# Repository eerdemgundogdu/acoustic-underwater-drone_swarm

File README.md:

# Akustik Suru Dugumu (acoustic-underwater-drone_swarm)

Deniz tabanina birakilan, aylarca pille bekleyen pasif akustik dinleme dugumu: gemi/arac gurultusuyle uyanir, pervane imzasini LOFAR ve DEMON ile cikarir, sonucu 24/28 kHz BFSK akustik modemle komsu dugumlere cok atlamali (multi-hop) olarak yayar. Uyku akimini piezo dalga/akinti hasadi destekler.

Sistem uc katmandan olusur:

- Donanim (`hardware/`): Teensy 4.1 tasiyici + hidrofon AFE + uyanma devresi + piezo hasadi + modem H-koprusu (2 katman, 120x95 mm, KiCad 9).
- Firmware (`firmware/`): 192 kHz cift ADC DMA ornekleme, akisli LOFAR/DEMON islemcileri, Goertzel tabanli BFSK alici, SipHash etiketli mesh protokolu ve guc durum makinesi.
- Model (`dsp/`): Bilesen degerlerinden AFE yaniti, uyku akim butcesi ve akustik baglanti butcesi; sematik ile firmware sabitlerinin tutarliligini test eder.

> **Durum:** Kart Rev A tasarim asamasindadir; uretilmedi ve donanimda test edilmedi. DSP ve modem zinciri sentetik sinyallerle (192 kHz) host testlerinde dogrulandi; firmware Teensy 4.1 icin derlenir. IFF kural seti bir demodur, saha imza kutuphanesi degildir.

## Calisma Dongusu

1. Uykuda yalnizca hep acik alan (~7 uA) calisir: `MCP6042` iki kademe ~60 dB (5..450 Hz) + tepe dedektoru + `TLV7031` karsilastirici.
2. Esik asilinca karsilastirici `LMR16006X` buck'i acar; RC mandal Teensy acilisina (~0.4 s) kadar gucu tutar, Teensy `PWR_HOLD` (pin 23) ile devralir.
3. Teensy, AFE'nin 20 dB ve 40 dB cikislarini ADC0/ADC1'de ayni anda 192 kHz'te DMA ile ornekler; `DualGainSelector` kirpilmayan kanali secer.
4. LOFAR (~2 s) ve DEMON (~2.7 s) sonucu `classify_signature` ile siniflandirilir. Hedef bulunursa dugum kendi TDMA yuvasinda alarm yayinlar.
5. Komsu dugumlerden gelen cerceveler dogrulanir (CRC-16 + SipHash-2-4), TTL > 0 ise tekrar yayinlanir.
6. Son aktiviteden 30 s sonra `PWR_HOLD` birakilir; buck kapanir, kart uykuya doner.

## Firmware (`firmware/`)

- `acoustic_dsp.cpp`: Radix-2 FFT, Hanning, Two-Pass Split-Window CFAR beyazlatma.
  - `LofarProcessor`: 192 kHz -> (4. derece Butterworth, /16) -> (/6) 2 kHz, 1024 noktalik FFT, 4 spektrum ortalamasi, 20..700 Hz tepe arama.
  - `DemonProcessor`: 4..30 kHz bant geciren -> kare-yasasi zarf -> /64 ortalama -> (LP 150 Hz, /8) 375 Hz -> 1024 noktalik FFT. Saft (2.5..11.5 Hz) ve N = 3..7 kanat harmonigi; yanlis alarm olasiligi ~7e-4 olacak sekilde 10 dB esik.
  - `DualGainSelector`: 20/40 dB AFE kanal secimi, kirpilma sonrasi 256 ornek histerezis.
- `dsp_filter.cpp`: RBJ biquad, 4. derece Butterworth, desimatorler.
- `bfsk_modem.cpp`: Verici bit plani (16 bit preamble + cerceve). Alicida 192 noktalik Goertzel (24/28 kHz tonlar + 20/32 kHz bant disi gurultu referansi), ceyrek sembol adimli 4 zamanlama seridi, `0xA55A` senkron kelimesi, verici sirasinda alici susturma.
- `swarm_mesh.cpp`: 20 baytlik cerceve, SipHash-2-4 (128 bit anahtar, 32 bit etiket) + CRC-16-CCITT, (kaynak, sira) halka tamponuyla tekrar eleme, TTL ile cok atlamali aktarim, dugum kimligine gore 250 ms TDMA yuvasi.
- `power_manager.cpp`: `BOOT / LISTEN / SHUTDOWN / FAULT_LEAK / LOW_BATT` durum makinesi; dinleme penceresi, alarm hiz siniri, sizintida periyodik alarm, dusuk pilde kapanma.
- `teensy_node/main.cpp`: Teensy entegrasyonu (`ADC` + `AnalogBufferDMA`, `IntervalTimer` ile sembol sembol BFSK yayini).

## Donanim (`hardware/`)

- 4S Li-ion girisi: 2 A sigorta, seri NC reed kurma anahtari, SS26 ters kutup, SMBJ20CA TVS.
- Hep acik alan: `HT7533-1` (30 V giris, 2.5 uA) ve piezo hasadi (BAT54S kopru + 22 uF + 18 V kiskac + ikinci `HT7533-1`), `BAT54C` diyot-VEYA.
- Uyanma mandali: `WAKE_CMP` VEYA `PWR_HOLD` -> 1 s RC -> `LMR16006X` `EN`.
- Hidrofon AFE: `MCP6022` x2, 20 dB + Sallen-Key 39.7 kHz (Q 0.74) + 20 dB, 100 ohm / 2.2 nF ADC surme ve BAT54S kiskaclari; `LP5907` dusuk gurultulu analog besleme.
- Modem vericisi: `DRV8871`, FlexPWM 24/28 kHz, 62k ILIM (~1 A), DC blok kondansatoru; eslesme trafosu ve projektor kart disi.
- Uykuda sifir akimli pil olcumu (`AO3401A` + `2N7002` yuksek taraf anahtari).

Tasarim hesaplari `hardware/DESIGN.md`, konnektor tablolari `hardware/WIRING.md`, uretim dosyalari (Gerber, BOM, CPL, sematik PDF, DRC raporu) `hardware/output/` altindadir.

## Derleme ve Testler

Donanim olmadan calisan C++ ve Python testleri:

```bash
cmake -S firmware/test -B build/test && cmake --build build/test && ctest --test-dir build/test --output-on-failure

python3 dsp/test_node_model.py
python3 dsp/node_model.py          # AFE yaniti, akim butcesi, baglanti butcesi ozeti
```

Teensy 4.1 derlemesi:

```bash
cd firmware
pio run -e node      # Rev A kart: uyanma/uyku dongusu
pio run -e bench     # Tezgah: USB beslemede surekli uyanik
```

Saha icin suru anahtari uretme:

```bash
python3 scripts/gen_swarm_key.py      # build_flags satirini yazar
```

Tezgah testi adimlari: `docs/tezgah_testi.md`.

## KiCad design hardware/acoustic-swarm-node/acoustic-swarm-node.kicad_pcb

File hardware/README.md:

# Akustik Suru Dugumu Karti (Rev A)

Teensy 4.1 tabanli pasif akustik dinleme / akustik modem dugumu icin 2 katmanli (120x95 mm, FR-4, 1.6 mm, 1 oz bakir) PCB tasarimi. Rev A tasarim asamasindadir; uretilmedi ve test edilmedi.

| Ust yuz | Izometrik |
| --- | --- |
|  |  |

| Alt yuz (GND dokumu) | Bakir + silkscreen yerlesimi |
| --- | --- |
|  |  |

Gorseller KiCad 9 3B goruntuleyicisinden (`kicad-cli pcb render`) uretilmistir; Teensy 4.1 soketi icin 3B model olmadigindan sadece header pedleri gorunur.

Kartin cozdugu temel elektriksel noktalar:

- Uykuda Teensy, AFE ve modem tamamen enerjisiz; yalnizca ~7 uA'lik hep acik alan (`HT7533-1` + `MCP6042` 60 dB uyanma yukselteci + `TLV7031` karsilastirici) hidrofonu dinler ve `LMR16006X` buck'in `EN` pinini surer. Teensy acilinca `PWR_HOLD` (pin 23) ile kendi beslemesini tutar.
- Hidrofon AFE'si: 20 dB on yukseltec, 39.7 kHz Sallen-Key anti-aliasing filtresi ve 40 dB ikinci kademe. Iki cikis Teensy'nin iki ADC'sinde ayni anda 192 kHz'te orneklenir (cift kazanc, ~80 dB dinamik aralik).
- Piezo dalga/akinti hasadi: `BAT54S` tam dalga kopru, 22 uF depolama, 18 V kiskac ve ikinci `HT7533-1`; `BAT54C` diyot-VEYA ile hep acik alani besler.
- `DRV8871` H-koprusuyle 24/28 kHz BFSK akustik modem vericisi (1 A akim siniri, kullanilmadiginda < 1 uA uyku).
- Uykuda sifir akim ceken anahtarli pil olcumu (`AO3401A` + `2N7002`), seri NC reed kurma anahtari, 2 A sigorta, ters kutup ve TVS korumasi.

## Dizin Yapisi

- `DESIGN.md`: Devre hesaplari, akim butcesi, AFE ve baglanti butcesi, PCB kurallari, devreye alma.
- `WIRING.md`: Konnektor ve Teensy 4.1 pin eslemesi.
- `acoustic-swarm-node/`: KiCad proje, sematik ve PCB dosyalari.
- `output/`: Gerber + delik paketi, BOM, CPL (pick-and-place), sematik PDF ve DRC raporu.
- `images/`: 3B render ve yerlesim gorselleri.
- `gen/`: Tek kaynak netlist (`design.py`) uzerinden sematik ve PCB'yi ureten Python betikleri.

Yeniden uretmek icin (KiCad 9, `kiutils`, `numpy`, `scipy`):

```bash
cd hardware/gen
python3 build.py
```

Linux disinda KiCad yollari ortam degiskenleriyle verilir:

```bash
KICAD_SHARE="C:/Program Files/KiCad/9.0/share/kicad" KICAD_CLI="C:/Program Files/KiCad/9.0/bin/kicad-cli.exe" \
  "C:/Program Files/KiCad/9.0/bin/python.exe" build.py
```

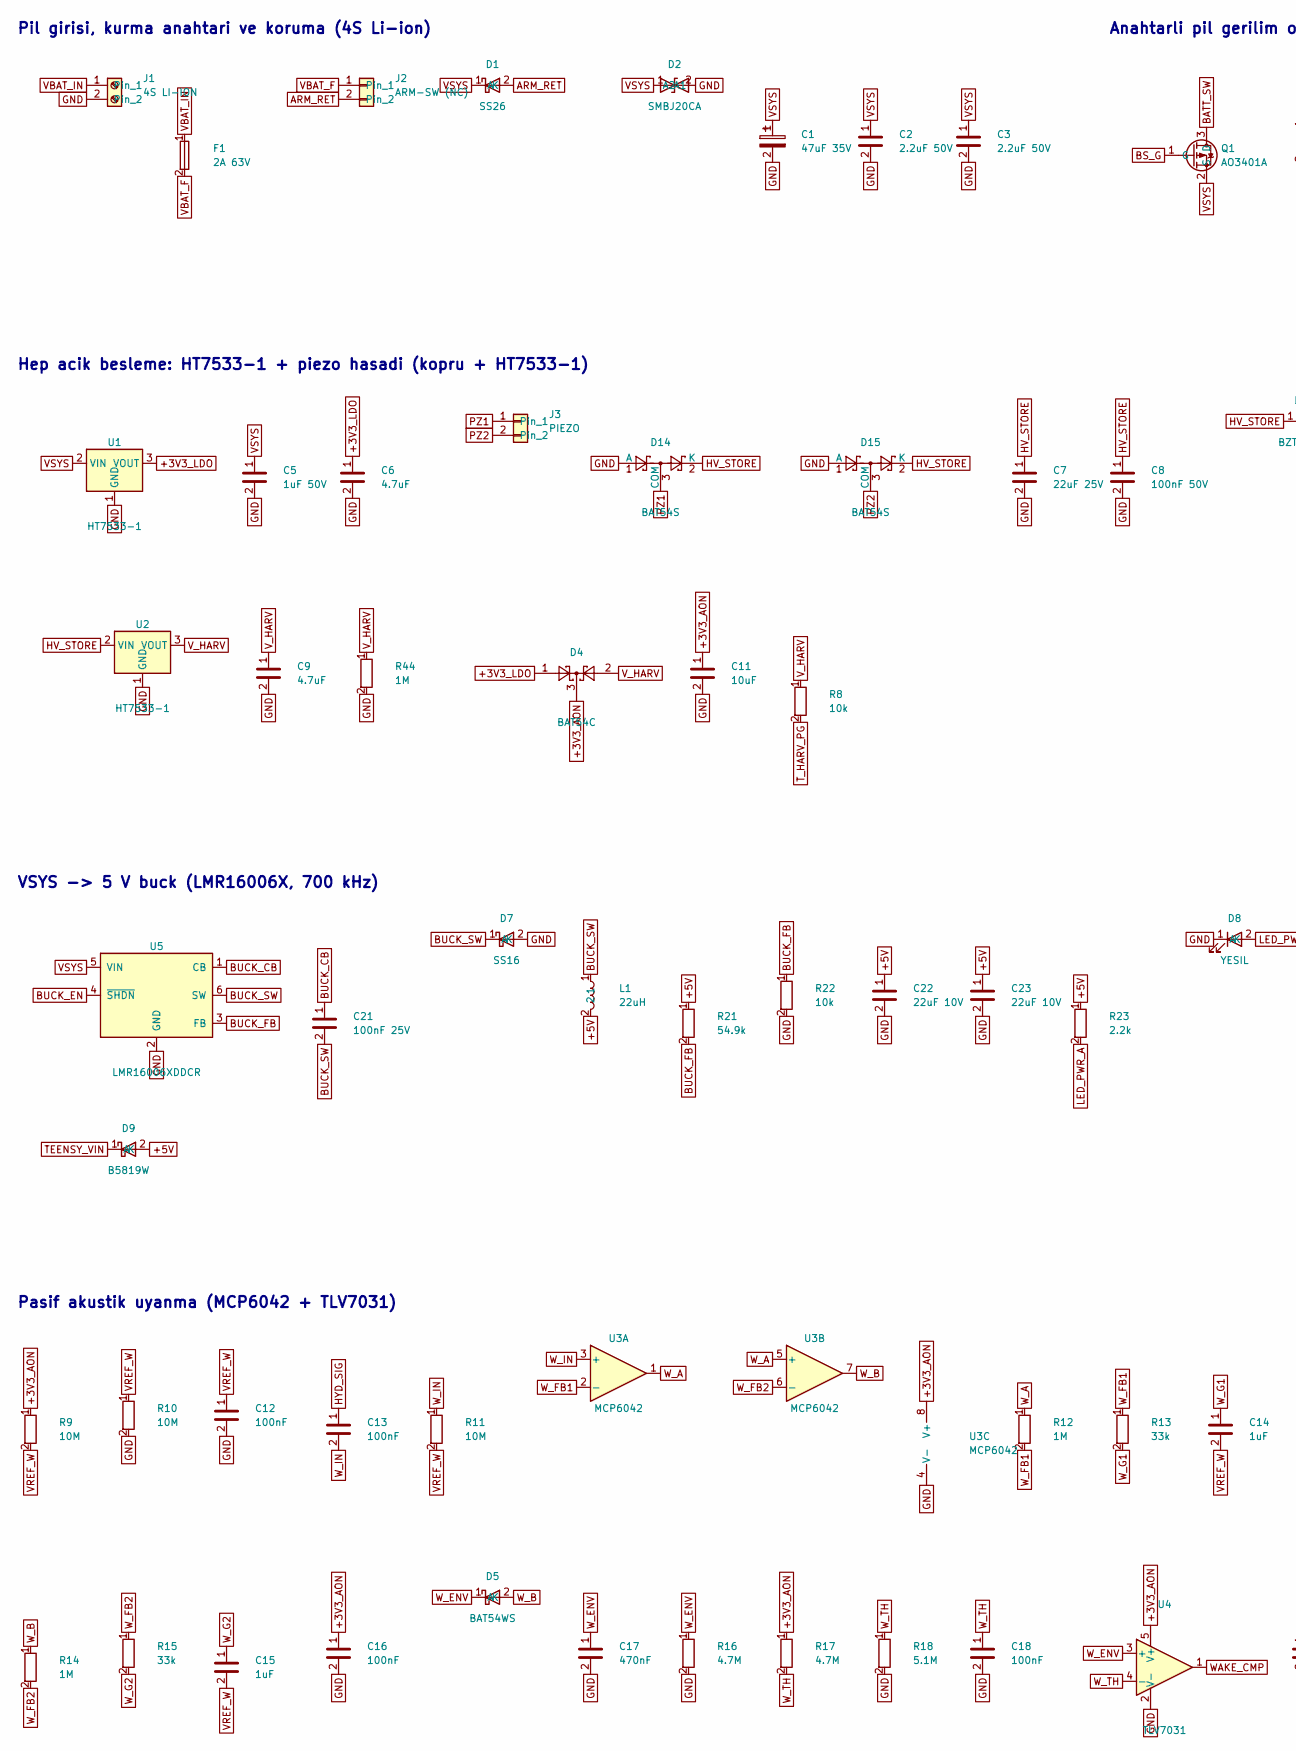
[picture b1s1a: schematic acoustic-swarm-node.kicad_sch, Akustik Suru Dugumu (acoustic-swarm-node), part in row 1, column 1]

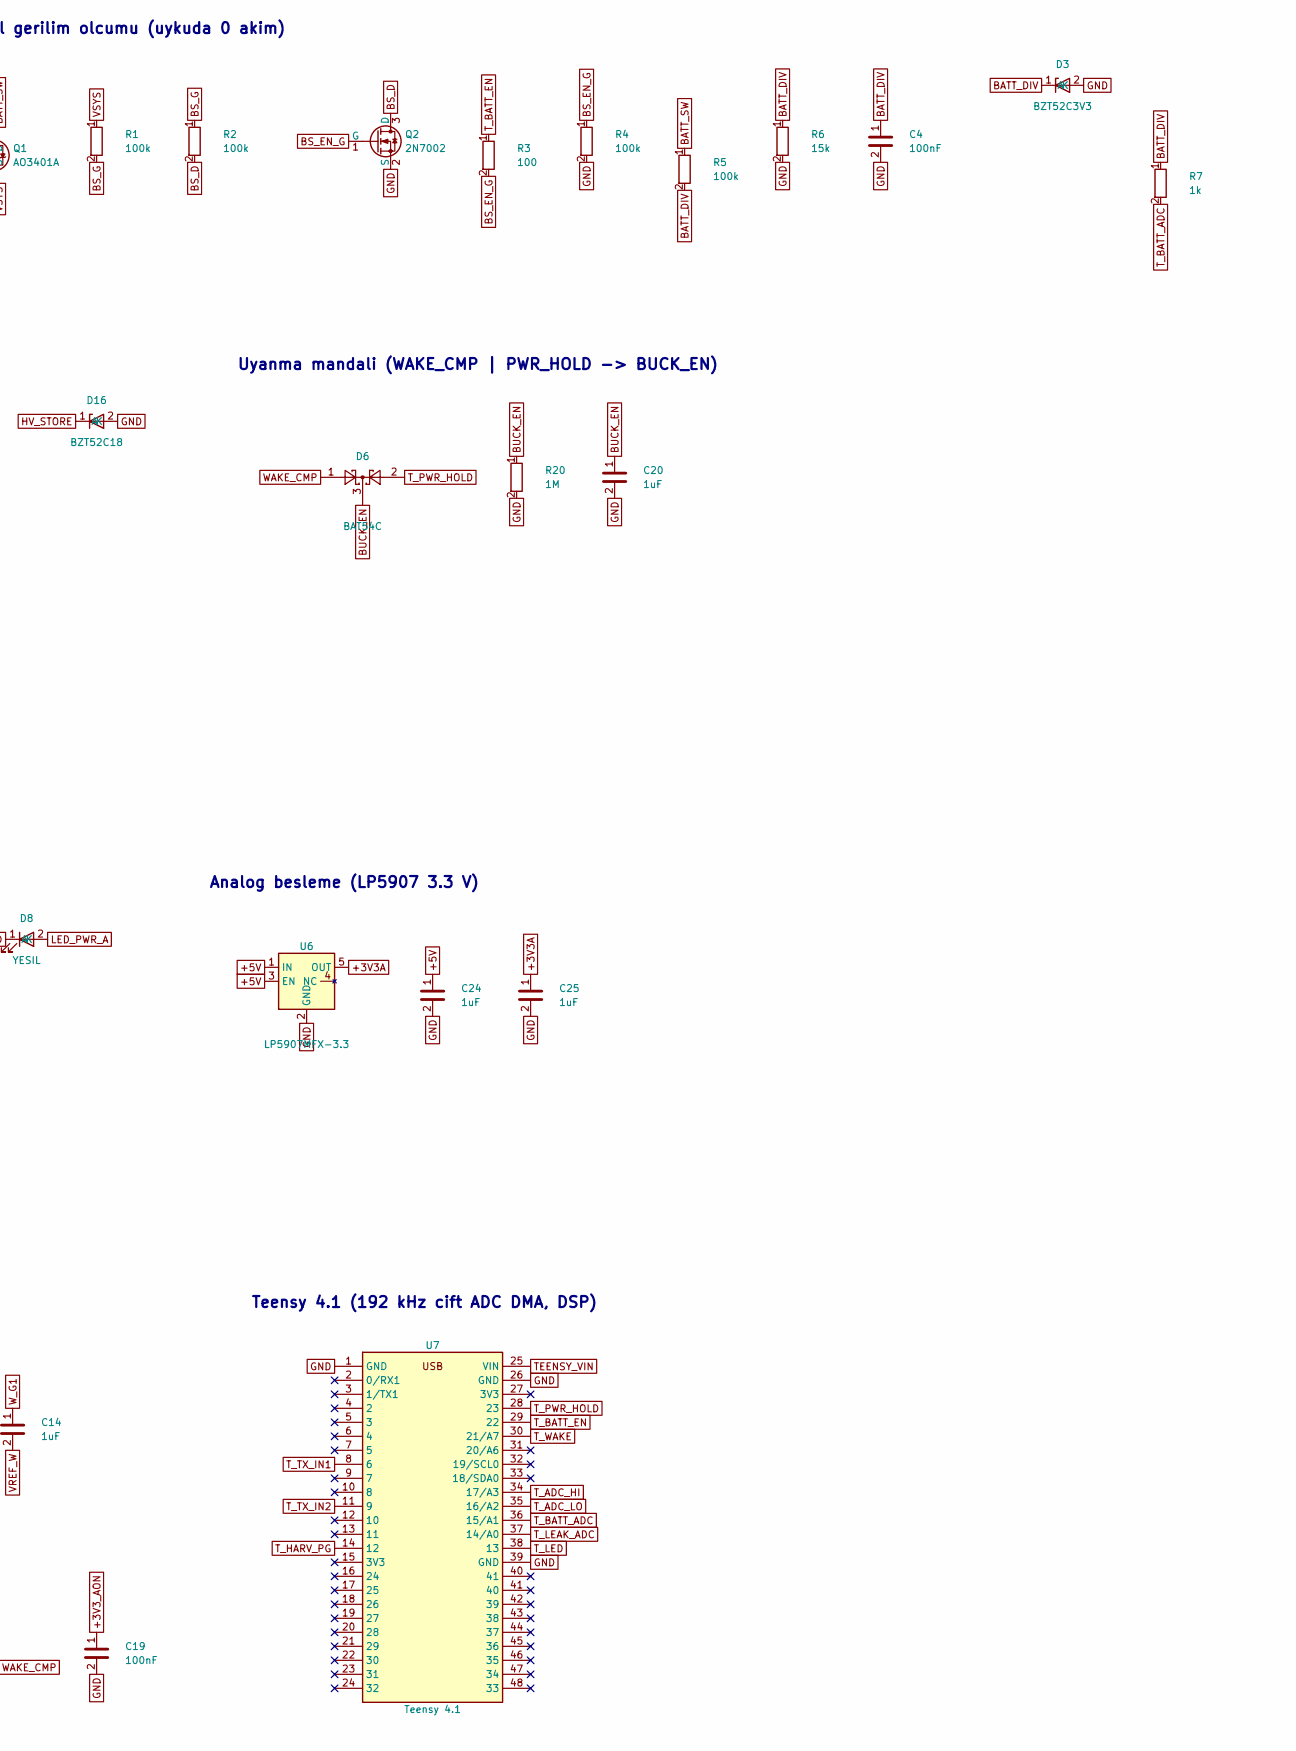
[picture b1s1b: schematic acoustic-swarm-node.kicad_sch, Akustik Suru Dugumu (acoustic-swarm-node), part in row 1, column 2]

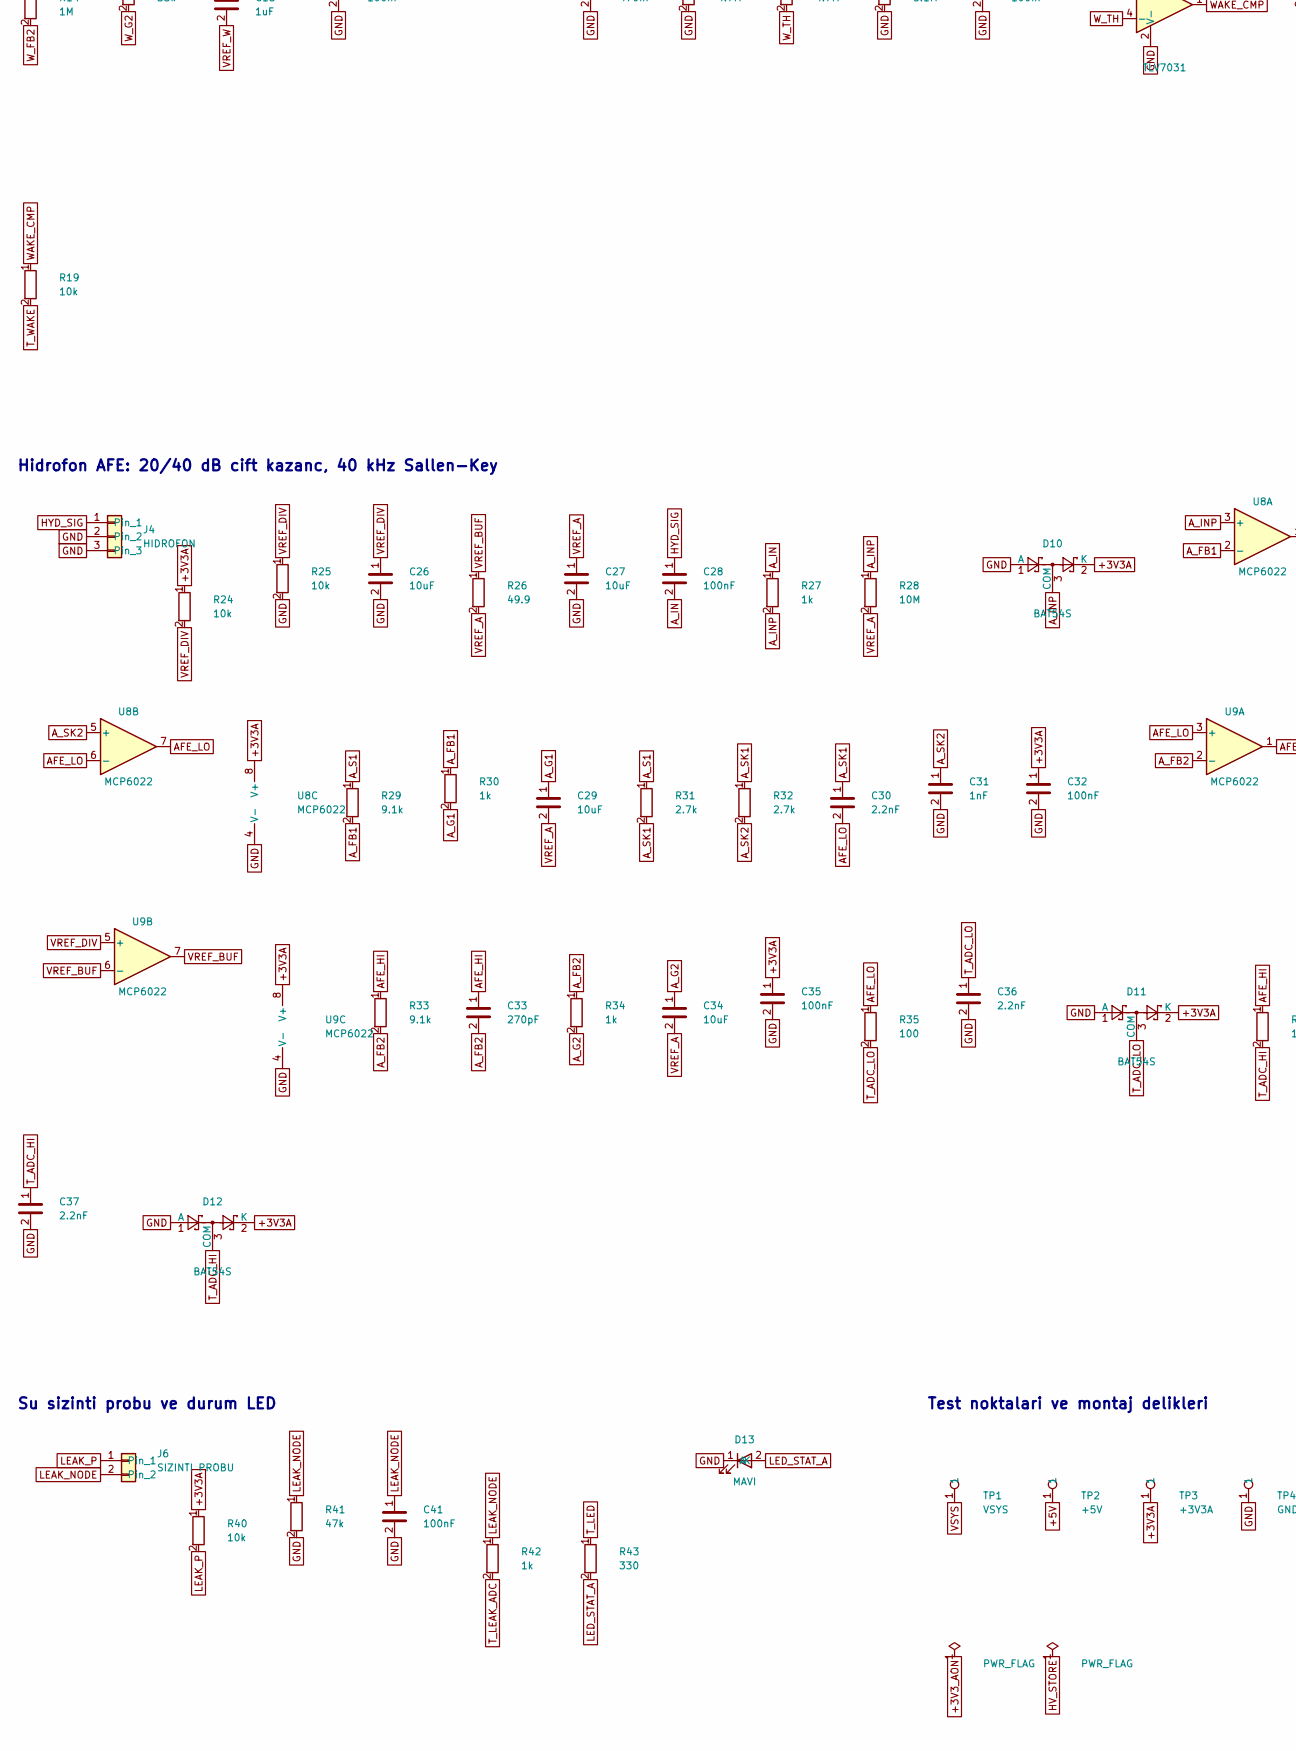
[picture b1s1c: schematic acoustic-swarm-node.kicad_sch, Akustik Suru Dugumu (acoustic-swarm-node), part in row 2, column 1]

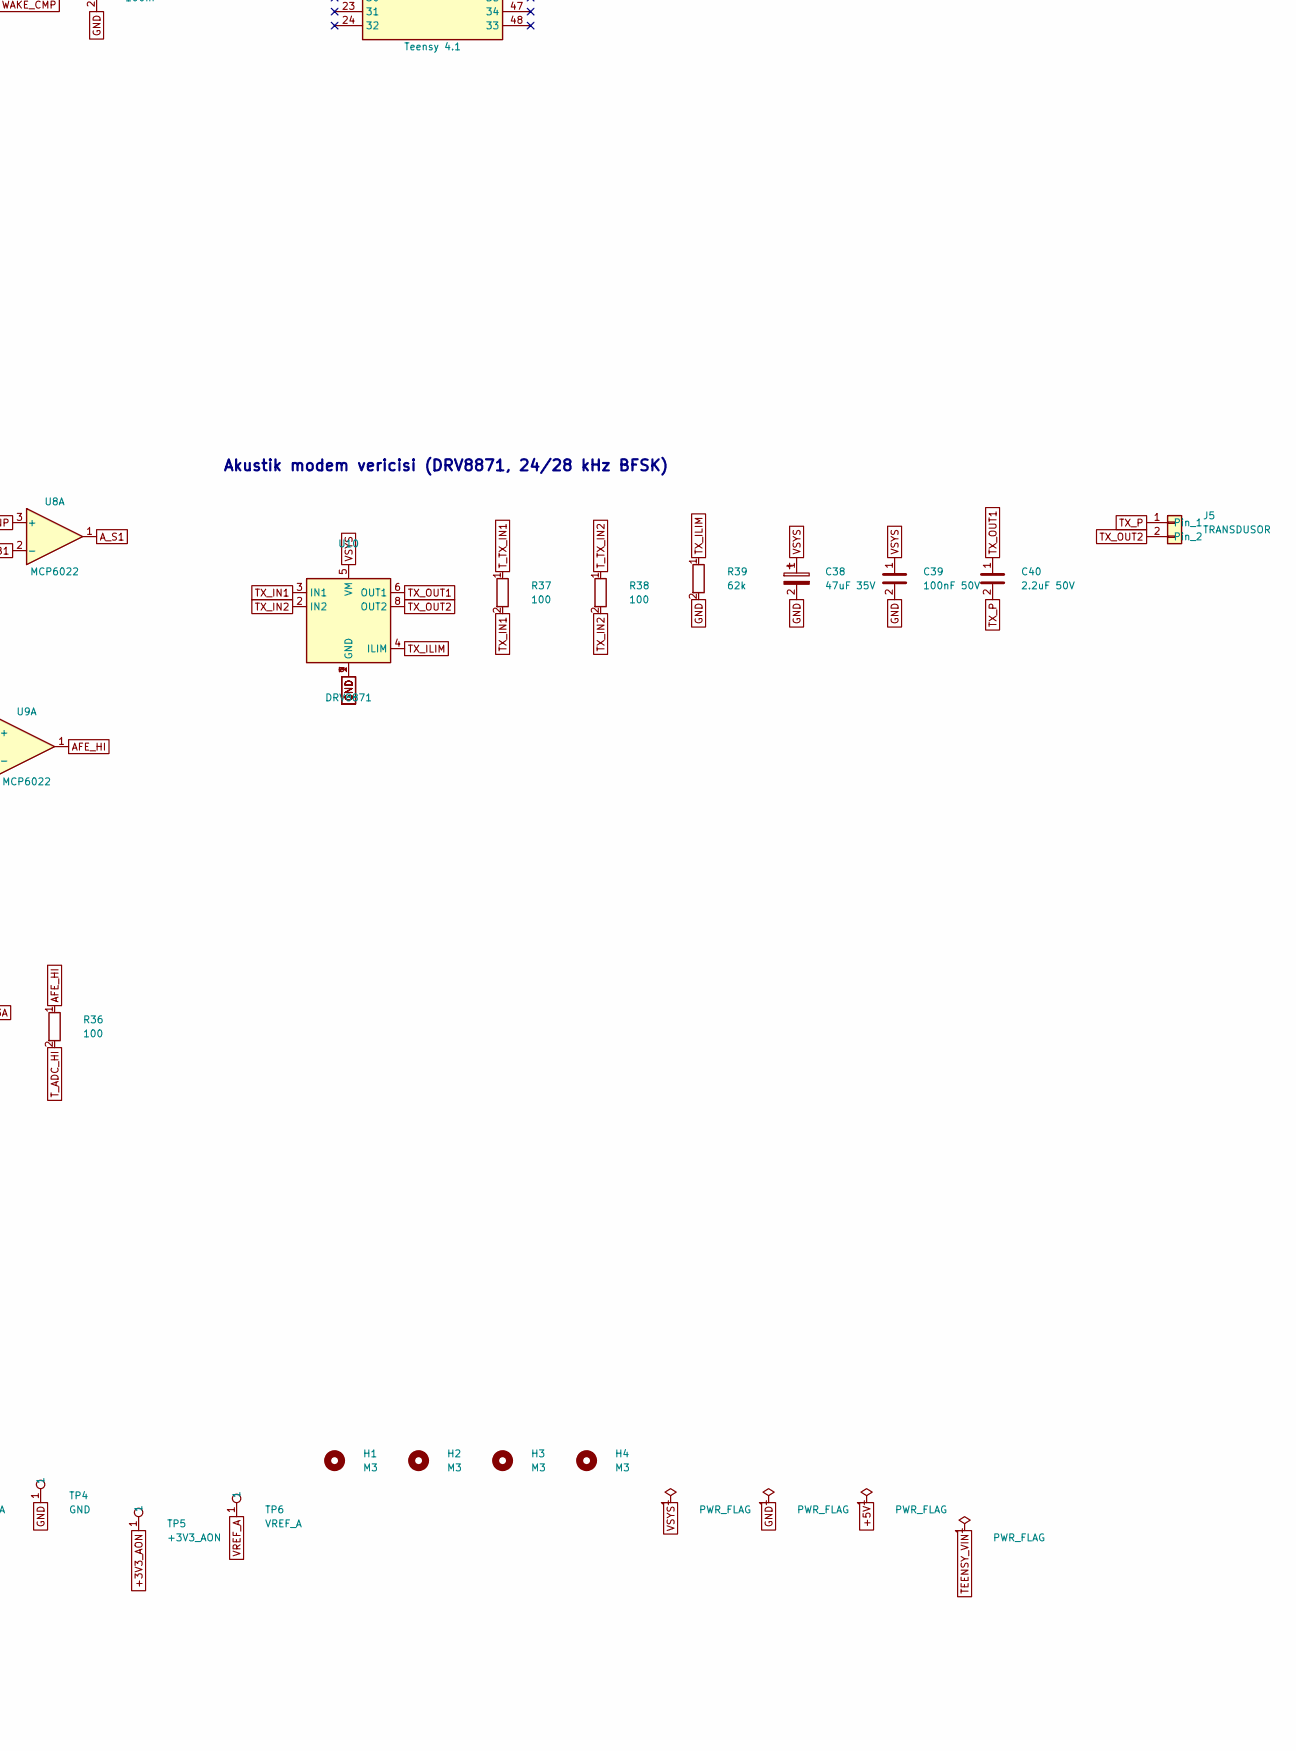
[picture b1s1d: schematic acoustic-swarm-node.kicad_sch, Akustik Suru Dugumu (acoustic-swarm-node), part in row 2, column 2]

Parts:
C1, C38: 47uF 35V; CP_Elec_6.3x7.7; MPN Panasonic EEE-FK1V470P
C2, C3, C40: 2.2uF 50V; C_1210_3225Metric; MPN X7R 1210 50V
C4, C12, C16, C18, C19, C32, C35, C41: 100nF; C_0603_1608Metric; MPN X7R 0603 16V
C5: 1uF 50V; C_1206_3216Metric; MPN X7R 1206 50V
C6, C9: 4.7uF; C_0805_2012Metric; MPN X5R 0805 10V
C7: 22uF 25V; C_1210_3225Metric; MPN X5R 1210 25V
C8, C39: 100nF 50V; C_0603_1608Metric; MPN X7R 0603 50V
C11, C26, C27, C29, C34: 10uF; C_0805_2012Metric; MPN X5R 0805 10V
C13, C28: 100nF; C_1206_3216Metric; MPN C0G/NP0 1206 50V
C14, C15, C20, C24, C25: 1uF; C_0603_1608Metric; MPN X7R 0603 16V
C17: 470nF; C_0603_1608Metric; MPN X7R 0603 16V
C21: 100nF 25V; C_0603_1608Metric; MPN X7R 0603 25V
C22, C23: 22uF 10V; C_1206_3216Metric; MPN X7R 1206 10V
C30, C36, C37: 2.2nF; C_0603_1608Metric; MPN C0G 0603 50V
C31: 1nF; C_0603_1608Metric; MPN C0G 0603 50V
C33: 270pF; C_0603_1608Metric; MPN C0G 0603 50V
D1: SS26; D_SMA; MPN SS26 (60V 2A)
D2: SMBJ20CA; D_SMB; MPN Littelfuse SMBJ20CA
D3: BZT52C3V3; D_SOD-123; MPN BZT52C3V3
D4, D6: BAT54C; SOT-23; MPN BAT54C
D5: BAT54WS; D_SOD-323; MPN Diodes BAT54WS
D7: SS16; D_SMA; MPN SS16 (60V 1A)
D8: YESIL; LED_0603_1608Metric; MPN 0603 yesil LED
D9: B5819W; D_SOD-123; MPN B5819W (40V 1A)
D10, D11, D12, D14, D15: BAT54S; SOT-23; MPN BAT54S
D13: MAVI; LED_0603_1608Metric; MPN 0603 mavi LED
D16: BZT52C18; D_SOD-123; MPN BZT52C18
F1: 2A 63V; Fuse_1206_3216Metric; MPN Littelfuse 0466002.NRHF
H1, H2, H3, H4: M3; MountingHole_3.2mm_M3
J1: 4S LI-ION; TerminalBlock_Phoenix_MKDS-1,5-2-5.08_1x02_P5.08mm_Horizont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; MPN Phoenix 1715721
J2: ARM-SW (NC); JST_XH_B2B-XH-A_1x02_P2.50mm_Vertical; MPN JST B2B-XH-A
J3: PIEZO; JST_XH_B2B-XH-A_1x02_P2.50mm_Vertical; MPN JST B2B-XH-A
J4: HIDROFON; JST_XH_B3B-XH-A_1x03_P2.50mm_Vertical; MPN JST B3B-XH-A
J5: TRANSDUSOR; JST_XH_B2B-XH-A_1x02_P2.50mm_Vertical; MPN JST B2B-XH-A
J6: SIZINTI PROBU; JST_XH_B2B-XH-A_1x02_P2.50mm_Vertical; MPN JST B2B-XH-A
L1: 22uH; L_Bourns_SRN6045TA; MPN Bourns SRN6045TA-220M
Q1: AO3401A; SOT-23; MPN AOS AO3401A
Q2: 2N7002; SOT-23; MPN Nexperia 2N7002
R1, R2, R4, R5: 100k; R_0603_1608Metric; MPN 0603 100k 1%
R3, R35, R36, R37, R38: 100; R_0603_1608Metric; MPN 0603 100 1%
R6: 15k; R_0603_1608Metric; MPN 0603 15k 1%
R7, R27, R30, R34, R42: 1k; R_0603_1608Metric; MPN 0603 1k 1%
R8, R19, R22, R24, R25, R40: 10k; R_0603_1608Metric; MPN 0603 10k 1%
R9, R10, R11, R28: 10M; R_0603_1608Metric; MPN 0603 10M 1%
R12, R14, R20, R44: 1M; R_0603_1608Metric; MPN 0603 1M 1%
R13, R15: 33k; R_0603_1608Metric; MPN 0603 33k 1%
R16, R17: 4.7M; R_0603_1608Metric; MPN 0603 4.7M 1%
R18: 5.1M; R_0603_1608Metric; MPN 0603 5.1M 1%
R21: 54.9k; R_0603_1608Metric; MPN 0603 54.9k 1%
R23: 2.2k; R_0603_1608Metric; MPN 0603 2.2k 1%
R26: 49.9; R_0603_1608Metric; MPN 0603 49.9 1%
R29, R33: 9.1k; R_0603_1608Metric; MPN 0603 9.1k 1%
R31, R32: 2.7k; R_0603_1608Metric; MPN 0603 2.7k 1%
R39: 62k; R_0603_1608Metric; MPN 0603 62k 1%
R41: 47k; R_0603_1608Metric; MPN 0603 47k 1%
R43: 330; R_0603_1608Metric; MPN 0603 330 1%
TP1: VSYS; TestPoint_Pad_D1.5mm
TP2: +5V; TestPoint_Pad_D1.5mm
TP3: +3V3A; TestPoint_Pad_D1.5mm
TP4: GND; TestPoint_Pad_D1.5mm
TP5: +3V3_AON; TestPoint_Pad_D1.5mm
TP6: VREF_A; TestPoint_Pad_D1.5mm
U1, U2: HT7533-1; SOT-89-3; MPN Holtek HT7533-1
U3: MCP6042; SOIC-8_3.9x4.9mm_P1.27mm; MPN Microchip MCP6042-I/SN
U4: TLV7031; SOT-23-5; MPN TI TLV7031DBVR
U5: LMR16006XDDCR; SOT-23-6; MPN TI LMR16006XDDCR
U6: LP5907MFX-3.3; SOT-23-5; MPN TI LP5907MFX-3.3
U7: Teensy 4.1; Teensy4.1_Socket; MPN PJRC Teensy 4.1 + 2x 1x24 disi header
U8, U9: MCP6022; SOIC-8_3.9x4.9mm_P1.27mm; MPN Microchip MCP6022-I/SN
U10: DRV8871; Texas_HTSOP-8-1EP_3.9x4.9mm_P1.27mm_EP2.95x4.9mm_Mask2.4x3.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; MPN TI DRV8871DDAR

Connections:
+3V3A: C25.1, C32.1, C35.1, D10.2 (K), D11.2 (K), D12.2 (K), R24.1, R40.1, TP3.1, U6.5 (OUT), U8.8 (V+), U9.8 (V+)
+3V3_AON: C11.1, C16.1, C19.1, D4.3, R9.1, R17.1, TP5.1, U3.8 (V+), U4.5 (V+)
+3V3_LDO: C6.1, D4.1, U1.3 (VOUT)
+5V: C22.1, C23.1, C24.1, D9.2 (A), L1.2, R21.1, R23.1, TP2.1, U6.1 (IN), U6.3 (EN)
AFE_HI: C33.1, R33.1, R36.1, U9.1
AFE_LO: C30.2, R35.1, U8.6 (-), U8.7, U9.3 (+)
ARM_RET: D1.2 (A), J2.2
A_FB1: R29.2, R30.1, U8.2 (-)
A_FB2: C33.2, R33.2, R34.1, U9.2 (-)
A_G1: C29.1, R30.2
A_G2: C34.1, R34.2
A_IN: C28.2, R27.1
A_INP: D10.3 (COM), R27.2, R28.1, U8.3 (+)
A_S1: R29.1, R31.1, U8.1
A_SK1: C30.1, R31.2, R32.1
A_SK2: C31.1, R32.2, U8.5 (+)
BATT_DIV: C4.1, D3.1 (K), R5.2, R6.1, R7.1
BATT_SW: Q1.3 (D), R5.1
BS_D: Q2.3 (D), R2.2
BS_EN_G: Q2.1 (G), R3.2, R4.1
BS_G: Q1.1 (G), R1.2, R2.1
BUCK_CB: C21.1, U5.1 (CB)
BUCK_EN: C20.1, D6.3, R20.1, U5.4 (~SHDN)
BUCK_FB: R21.2, R22.1, U5.3 (FB)
BUCK_SW: C21.2, D7.1 (K), L1.1, U5.6 (SW)
GND: C1.2, C2.2, C3.2, C4.2, C5.2, C6.2, C7.2, C8.2, C9.2, C11.2, C12.2, C16.2, C17.2, C18.2, C19.2, C20.2, C22.2, C23.2, C24.2, C25.2, C26.2, C27.2, C31.2, C32.2, C35.2, C36.2, C37.2, C38.2, C39.2, C41.2, D2.2 (A2), D3.2 (A), D7.2 (A), D8.1 (K), D10.1 (A), D11.1 (A), D12.1 (A), D13.1 (K), D14.1 (A), D15.1 (A), D16.2 (A), J1.2, J4.2, J4.3, Q2.2 (S), R4.2, R6.2, R10.2, R16.2, R18.2, R20.2, R22.2, R25.2, R39.2, R41.2, R44.2, TP4.1, U1.1 (GND), U2.1 (GND), U3.4 (V-), U4.2 (V-), U5.2 (GND), U6.2 (GND), U7.1 (GND), U7.26 (GND), U7.39 (GND), U8.4 (V-), U9.4 (V-), U10.1 (GND), U10.7 (GND), U10.9 (GND)
HV_STORE: C7.1, C8.1, D14.2 (K), D15.2 (K), D16.1 (K), U2.2 (VIN)
HYD_SIG: C13.1, C28.1, J4.1
LEAK_NODE: C41.1, J6.2, R41.1, R42.1
LEAK_P: J6.1, R40.2
LED_PWR_A: D8.2 (A), R23.2
LED_STAT_A: D13.2 (A), R43.2
PZ1: D14.3 (COM), J3.1
PZ2: D15.3 (COM), J3.2
TEENSY_VIN: D9.1 (K), U7.25 (VIN)
TX_ILIM: R39.1, U10.4 (ILIM)
TX_IN1: R37.2, U10.3 (IN1)
TX_IN2: R38.2, U10.2 (IN2)
TX_OUT1: C40.1, U10.6 (OUT1)
TX_OUT2: J5.2, U10.8 (OUT2)
TX_P: C40.2, J5.1
T_ADC_HI: C37.1, D12.3 (COM), R36.2, U7.34 (17/A3)
T_ADC_LO: C36.1, D11.3 (COM), R35.2, U7.35 (16/A2)
T_BATT_ADC: R7.2, U7.36 (15/A1)
T_BATT_EN: R3.1, U7.29 (22)
T_HARV_PG: R8.2, U7.14 (12)
T_LEAK_ADC: R42.2, U7.37 (14/A0)
T_LED: R43.1, U7.38 (13)
T_PWR_HOLD: D6.2, U7.28 (23)
T_TX_IN1: R37.1, U7.8 (6)
T_TX_IN2: R38.1, U7.11 (9)
T_WAKE: R19.2, U7.30 (21/A7)
VBAT_F: F1.2, J2.1
VBAT_IN: F1.1, J1.1
VREF_A: C27.1, C29.2, C34.2, R26.2, R28.2, TP6.1
VREF_BUF: R26.1, U9.6 (-), U9.7
VREF_DIV: C26.1, R24.2, R25.1, U9.5 (+)
VREF_W: C12.1, C14.2, C15.2, R9.2, R10.1, R11.2
VSYS: C1.1, C2.1, C3.1, C5.1, C38.1, C39.1, D1.1 (K), D2.1 (A1), Q1.2 (S), R1.1, TP1.1, U1.2 (VIN), U5.5 (VIN), U10.5 (VM)
V_HARV: C9.1, D4.2, R8.1, R44.1, U2.3 (VOUT)
WAKE_CMP: D6.1, R19.1, U4.1
W_A: R12.1, U3.1, U3.5 (+)
W_B: D5.2 (A), R14.1, U3.7
W_ENV: C17.1, D5.1 (K), R16.1, U4.3 (+)
W_FB1: R12.2, R13.1, U3.2 (-)
W_FB2: R14.2, R15.1, U3.6 (-)
W_G1: C14.1, R13.2
W_G2: C15.1, R15.2
W_IN: C13.2, R11.1, U3.3 (+)
W_TH: C18.1, R17.2, R18.1, U4.4 (-)

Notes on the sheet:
Pil girisi, kurma anahtari ve koruma (4S Li-ion)
Anahtarli pil gerilim olcumu (uykuda 0 akim)
Hep acik besleme: HT7533-1 + piezo hasadi (kopru + HT7533-1)
Uyanma mandali (WAKE_CMP | PWR_HOLD -> BUCK_EN)
VSYS -> 5 V buck (LMR16006X, 700 kHz)
Analog besleme (LP5907 3.3 V)
Pasif akustik uyanma (MCP6042 + TLV7031)
Teensy 4.1 (192 kHz cift ADC DMA, DSP)
Hidrofon AFE: 20/40 dB cift kazanc, 40 kHz Sallen-Key
Akustik modem vericisi (DRV8871, 24/28 kHz BFSK)
Su sizinti probu ve durum LED
Test noktalari ve montaj delikleri

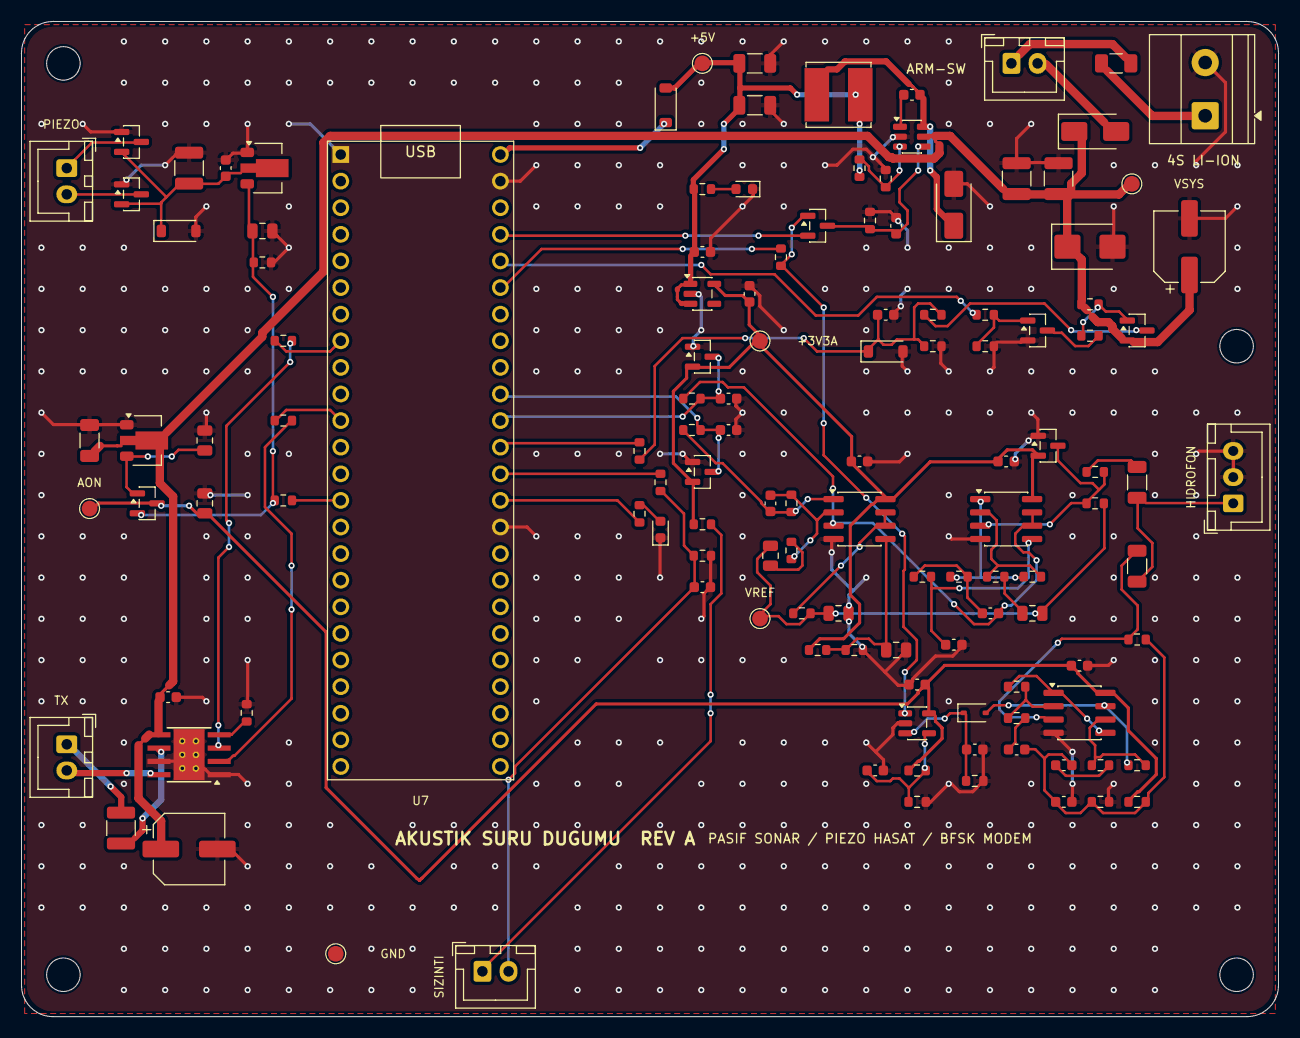
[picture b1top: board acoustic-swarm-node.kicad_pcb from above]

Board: 2 copper layers, 120.0 x 95.0 mm, 130 parts (0 on the bottom side), 70 nets.

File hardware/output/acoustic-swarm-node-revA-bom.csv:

Adet,Referanslar,Deger,Footprint,Parca,Not
2,C1 C38,47uF 35V,CP_Elec_6.3x7.7,Panasonic EEE-FK1V470P,H-koprusu VM toplu kapasite; Toplu giris kondansatoru
3,C2 C3 C40,2.2uF 50V,C_1210_3225Metric,X7R 1210 50V,
8,C4 C12 C16 C18 C19 C32 C35 C41,100nF,C_0603_1608Metric,X7R 0603 16V,
1,C5,1uF 50V,C_1206_3216Metric,X7R 1206 50V,
2,C6 C9,4.7uF,C_0805_2012Metric,X5R 0805 10V,
1,C7,22uF 25V,C_1210_3225Metric,X5R 1210 25V,
2,C8 C39,100nF 50V,C_0603_1608Metric,X7R 0603 50V,
5,C11 C26 C27 C29 C34,10uF,C_0805_2012Metric,X5R 0805 10V,
2,C13 C28,100nF,C_1206_3216Metric,C0G/NP0 1206 50V,
5,C14 C15 C20 C24 C25,1uF,C_0603_1608Metric,X7R 0603 16V,
1,C17,470nF,C_0603_1608Metric,X7R 0603 16V,
1,C21,100nF 25V,C_0603_1608Metric,X7R 0603 25V,
2,C22 C23,22uF 10V,C_1206_3216Metric,X7R 1206 10V,
3,C30 C36 C37,2.2nF,C_0603_1608Metric,C0G 0603 50V,
1,C31,1nF,C_0603_1608Metric,C0G 0603 50V,
1,C33,270pF,C_0603_1608Metric,C0G 0603 50V,
1,D1,SS26,D_SMA,SS26 (60V 2A),Ters kutup korumasi
1,D2,SMBJ20CA,D_SMB,Littelfuse SMBJ20CA,Vrwm 20V > 16.8V tam dolu; transdusor geri tepme kiskaci
1,D3,BZT52C3V3,D_SOD-123,BZT52C3V3,ADC 3.3 V kiskaci
2,D4 D6,BAT54C,SOT-23,BAT54C,Diyot-VEYA: yuksek olan kaynak AON alanini besler
1,D5,BAT54WS,D_SOD-323,Diodes BAT54WS,Tepe (zarf) dedektoru
1,D7,SS16,D_SMA,SS16 (60V 1A),Buck serbest gecis (catch) diyodu
1,D8,YESIL,LED_0603_1608Metric,0603 yesil LED,+5V var (dugum uyanik)
1,D9,B5819W,D_SOD-123,B5819W (40V 1A),USB 5V ile kart 5V birbirini geri beslemesin
5,D10 D11 D12 D14 D15,BAT54S,SOT-23,BAT54S,"Giris asiri gerilim kiskaci; Pin 16 (A2) kiskaci; Pin 17 (A3) kiskaci; Tam dalga kopru, 1. kol; Tam dalga kopru, 2. kol"
1,D13,MAVI,LED_0603_1608Metric,0603 mavi LED,"Durum LED (pin 13, Teensy dahili LED ile paralel)"
1,D16,BZT52C18,D_SOD-123,BZT52C18,Depolama kiskaci: C7 25 V ve BAT54 30 V sinirlarinin altinda
1,F1,2A 63V,Fuse_1206_3216Metric,Littelfuse 0466002.NRHF,Modem H-koprusu tepe akimi (ILIM 1 A) + lojik
1,J1,4S LI-ION,"TerminalBlock_Phoenix_MKDS-1,5-2-5.08_1x02_P5.08mm_Horizontal",Phoenix 1715721,"4S Li-ion paket (BMS dahili), 12.0 - 16.8 V"
1,J2,ARM-SW (NC),JST_XH_B2B-XH-A_1x02_P2.50mm_Vertical,JST B2B-XH-A,Su gecirmez NC reed: tasima miknatisi takiliyken pil tamamen ayrik
1,J3,PIEZO,JST_XH_B2B-XH-A_1x02_P2.50mm_Vertical,JST B2B-XH-A,PVDF/PZT dalga-akinti hasat elemani (AC)
1,J4,HIDROFON,JST_XH_B3B-XH-A_1x03_P2.50mm_Vertical,JST B3B-XH-A,Pasif piezo hidrofon (-200 dB re 1V/uPa sinifi); pin 3 kablo ekrani
1,J5,TRANSDUSOR,JST_XH_B2B-XH-A_1x02_P2.50mm_Vertical,JST B2B-XH-A,Eslesme trafosu + 25 kHz rezonansli projektor (kart disi)
1,J6,SIZINTI PROBU,JST_XH_B2B-XH-A_1x02_P2.50mm_Vertical,JST B2B-XH-A,Tup ici iletken su sizinti elektrotlari
1,L1,22uH,L_Bourns_SRN6045TA,Bourns SRN6045TA-220M,Isat >= 1 A
1,Q1,AO3401A,SOT-23,AOS AO3401A,"Vds -30V, Vgs +-12V"
1,Q2,2N7002,SOT-23,Nexperia 2N7002,
4,R1 R2 R4 R5,100k,R_0603_1608Metric,0603 100k 1%,
5,R3 R35 R36 R37 R38,100,R_0603_1608Metric,0603 100 1%,
1,R6,15k,R_0603_1608Metric,0603 15k 1%,
5,R7 R27 R30 R34 R42,1k,R_0603_1608Metric,0603 1k 1%,
6,R8 R19 R22 R24 R25 R40,10k,R_0603_1608Metric,0603 10k 1%,
4,R9 R10 R11 R28,10M,R_0603_1608Metric,0603 10M 1%,
4,R12 R14 R20 R44,1M,R_0603_1608Metric,0603 1M 1%,
2,R13 R15,33k,R_0603_1608Metric,0603 33k 1%,
2,R16 R17,4.7M,R_0603_1608Metric,0603 4.7M 1%,
1,R18,5.1M,R_0603_1608Metric,0603 5.1M 1%,
1,R21,54.9k,R_0603_1608Metric,0603 54.9k 1%,
1,R23,2.2k,R_0603_1608Metric,0603 2.2k 1%,
1,R26,49.9,R_0603_1608Metric,0603 49.9 1%,
2,R29 R33,9.1k,R_0603_1608Metric,0603 9.1k 1%,
2,R31 R32,2.7k,R_0603_1608Metric,0603 2.7k 1%,
1,R39,62k,R_0603_1608Metric,0603 62k 1%,
1,R41,47k,R_0603_1608Metric,0603 47k 1%,
1,R43,330,R_0603_1608Metric,0603 330 1%,
2,U1 U2,HT7533-1,SOT-89-3,Holtek HT7533-1,"Hasat LDO: Iq 2.5 uA, depolama > ~3.5 V iken regule; Vin max 30 V, Iq 2.5 uA, 100 mA"
1,U3,MCP6042,SOIC-8_3.9x4.9mm_P1.27mm,Microchip MCP6042-I/SN,GBW 14 kHz; kademe kazanci 31.3 -> BW ~450 Hz
1,U4,TLV7031,SOT-23-5,TI TLV7031DBVR,"Push-pull, 335 nA"
1,U5,LMR16006XDDCR,SOT-23-6,TI LMR16006XDDCR,X versiyonu (700 kHz); sembol Y ile pin uyumlu
1,U6,LP5907MFX-3.3,SOT-23-5,TI LP5907MFX-3.3,Dusuk gurultulu analog LDO
1,U7,Teensy 4.1,Teensy4.1_Socket,PJRC Teensy 4.1 + 2x 1x24 disi header,Tum 3.3V pinleri bos; VIN D9 uzerinden
2,U8 U9,MCP6022,SOIC-8_3.9x4.9mm_P1.27mm,Microchip MCP6022-I/SN,"B kanali Vref tamponu; GBW 10 MHz, 8.7 nV/rtHz, RRIO"
1,U10,DRV8871,Texas_HTSOP-8-1EP_3.9x4.9mm_P1.27mm_EP2.95x4.9mm_Mask2.4x3.1mm_ThermalVias,TI DRV8871DDAR,PWM <= 200 kHz; IN1=IN2=0 iken ~1 ms sonra uyku (<1 uA)
